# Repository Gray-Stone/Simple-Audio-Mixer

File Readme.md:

# Simple 2-in-1-out Audio Merger
 Design choices and reason for decision  

Overview 
=========

Core feature:
-------------

Simple Audio Merger (SAM) is designed to be used for merging audio from
2 sources and simply output the added voltage to output. Input is design
for common consumer appliances with stereo audio, and there will not be
any processing other than summation on board. The output is only
buffered (powered) by an Opamp, and a power amplifier should be used if
the load is not high impedance (headphone, speaker is typical low
impedance load).

Power Option
============

3.5mm stereo audio jack will be used as audio interface for both input
and output. This is the most common form of audio connection between
desktop device and is simplest.

Power source 
-------------

Possible choice of USB power and battery power.

Benefit of USB supply:

-   Device’s original design is to be used to merge audio from computer
    and gamming console, this means abundant USB supplies.

Problem with USB supply:

-   Huge amount of noise (USB data line, other USB devices, etc.)

-   Single Rail, and the lower rail is mains-earth reference (virtual
    ground cannot be connected with other devices)

Reason to choose battery supply:

-   Clean rail.

-   Easily generated negative rail (or virtual ground).

-   Since floating rail, no requirement before connecting ground with
    other device (virtual or not)

Problem with battery:

-   Need replace battery

-   Need a battery management system to detect low battery and
    shutoff/notice user before it causes problem

The USB high power rail noise is not much of a problem given all signal
goes through Opamp, which have great rail rejection.

The battery replacement is not that bad, this design does not provide
power amplifier. Most power are used by Opamp. So, replacement cycle is
not as often. In addition, audio signal is basically below 1V, two AA
battery will be enough for dual rails.

Both choices are ok, if a battery is chosen, then BMS is needed. If USB
is chosen, negative rail is needed.

Dual Rail generation 
---------------------

If USB power is used, a negative rail must be generated. Generate a half
rail virtual ground is not suitable in this case.

A voltage reference is generally generated by a voltage buffer with
input connect to a revers biased zener. The zener voltage is set by
current, despite little, but still fluctuate with current change. The
source current for zener voltage is usually set by resistor, which is
voltage controlled current.

USB is mains-earth referenced ground. The audio ground from other device
(input and output amplifier) is the same mains-earth reference as well.
This means the virtual ground can not be connected to another device.

When using virtual ground, the output voltage is referenced to virtual
ground. The voltage ripple across “negative rail” and virtual ground is
considered rail noise. However, since other device is also ground
referenced, they see they “negative rail” noise as a noise added to
virtual ground. Since output is referenced to virtual ground, outside
device also see this noise as part of the output signal (instead of
common mode noise).

If battery is used, then a virtual ground is easily generated by
connecting a lead from middle of the two batteries. This virtual ground
will be push pull and very stable in voltage. Furthermore, battery is
floating voltage device, the virtual ground can be connected to any
mains-earth connection. This connection makes it remove some common-mode
noise.

Merge Audio Signal
==================

Resistor Summing Circuit.
-------------------------

Audio signal are generally a voltage signal. One possible choice is to
connect everything through a resistor to a summing point. The resistor
turns the voltage signal into current signal. Then transconductance
amplifier can easily turn that into output voltage.

In this case, the impedance each input device see depends on the
resistance and other device it sees.

Individual Opamp Buffered.
--------------------------

If each input is first buffered by an opamp, then all input device sees
high impedance which is decoupled from others. In the case of a low
impedance (high power) device on input side, buffer Opamp prevent other
input device get loaded.

Decision
========

-   USB power source with negative rail (No BMS required, Opamp have
    good PSRR).

-   Opamp buffered input (Opamp are cheap, this is a one-off board).

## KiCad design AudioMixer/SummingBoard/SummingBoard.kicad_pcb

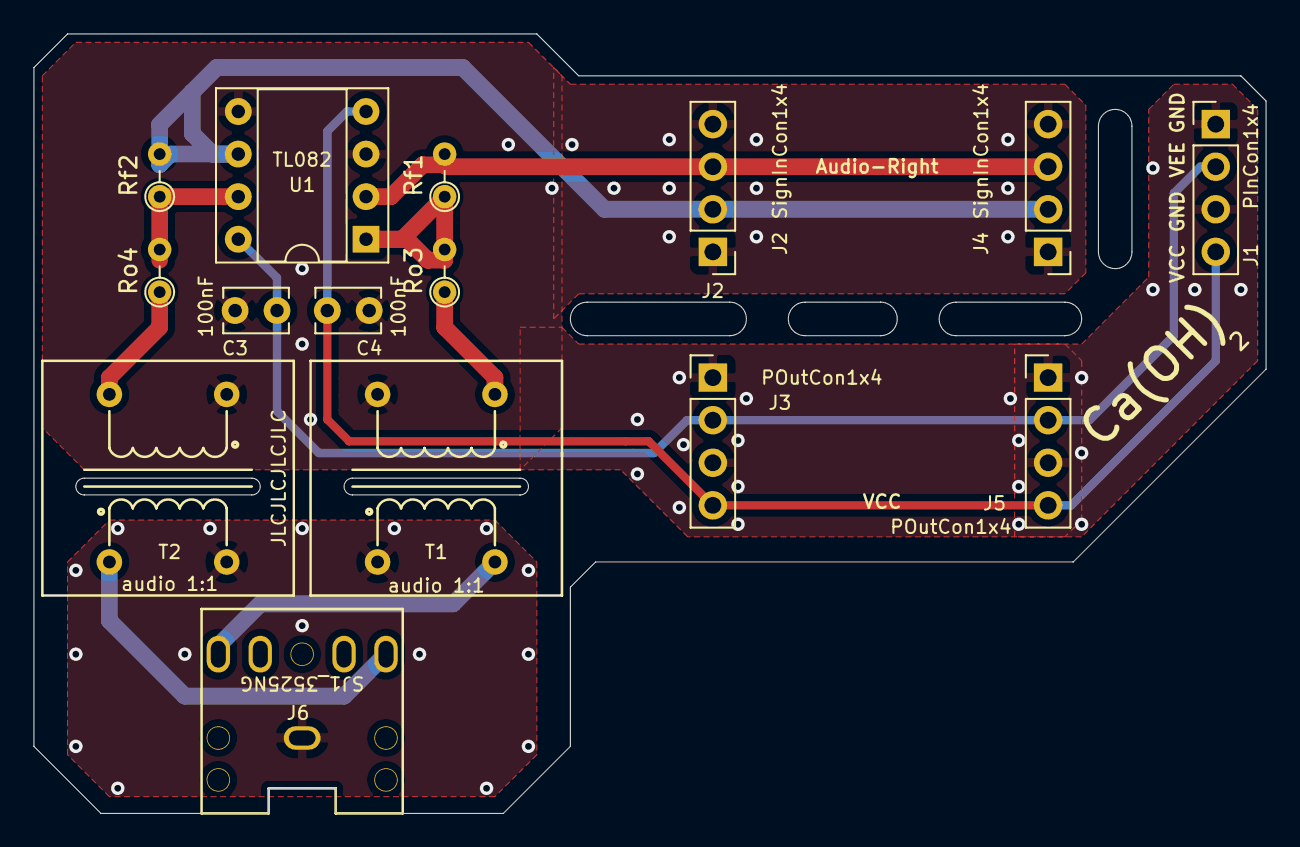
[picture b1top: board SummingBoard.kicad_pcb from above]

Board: 2 copper layers, 73.5 x 46.5 mm, 15 parts (0 on the bottom side), 12 nets.

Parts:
C3, C4: 100nF; C_Disc_D3.8mm_W2.6mm_P2.50mm
J1: PInCon1x4; Socket_Strip_Straight_1x04_Pitch2.54mm
J2, J4: SignInCon1x4; Socket_Strip_Straight_1x04_Pitch2.54mm
J3, J5: POutCon1x4; Socket_Strip_Straight_1x04_Pitch2.54mm
J6: SJ1_3525NG; Audio Barral SJ1-3525NG
Rf1, Rf2: 1k; R_Axial_DIN0204_L3.6mm_D1.6mm_P2.54mm_Vertical
Ro3, Ro4: 100; R_Axial_DIN0204_L3.6mm_D1.6mm_P2.54mm_Vertical
T1, T2: audio 1:1; Audio Transformer
U1: TL082; DIP-8_W7.62mm_Socket

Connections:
/Audio-Left: J2.2, J4.2, Rf2.2, U1.6
/Audio-Right: J2.3, J4.3, Rf1.2, U1.2
/Output_Ground: J6.1, T1.1, T2.2
GND: C3.2, C4.1, J1.1, J1.3, J2.1, J2.4, J3.1, J3.3, J4.1, J4.4, J5.1, J5.3, T1.3, T2.4, U1.3, U1.5
unnamed: J6.2, T2.1
unnamed: J6.3, T1.2
unnamed: Rf1.1, Ro3.2, U1.1
unnamed: Rf2.1, Ro4.2, U1.7
unnamed: Ro3.1, T1.4
unnamed: Ro4.1, T2.3
VCC: C3.1, J1.2, J3.2, J5.2, U1.8
VEE: C4.2, J1.4, J3.4, J5.4, U1.4

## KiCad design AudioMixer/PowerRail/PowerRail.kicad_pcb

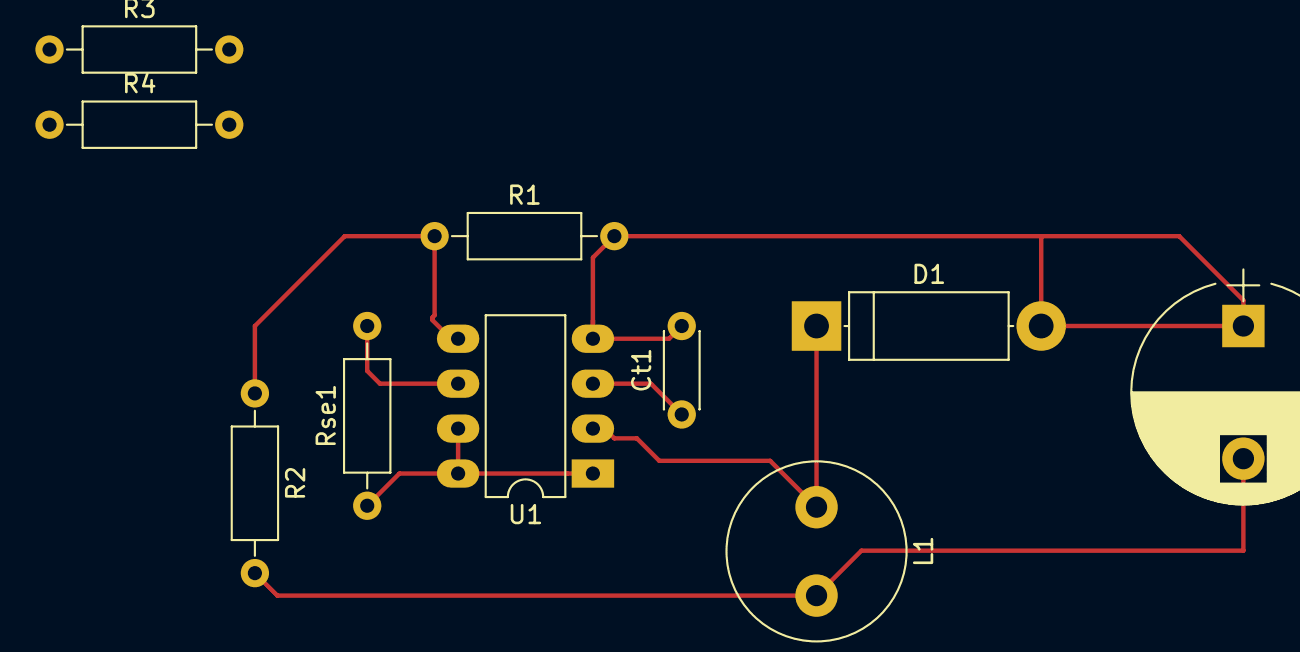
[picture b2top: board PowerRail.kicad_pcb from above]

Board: 2 copper layers, 10 parts (0 on the bottom side), 7 nets.

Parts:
Co1: 2585uF; CP_Radial_D12.5mm_P7.50mm
Ct1: 574pF; C_Disc_D4.3mm_W1.9mm_P5.00mm
D1: 1N4148; D_5W_P12.70mm_Horizontal
L1: 61uH; L_Radial_D10.0mm_P5.00mm_Neosid_SD12_style3
R1: 1k; R_Axial_DIN0207_L6.3mm_D2.5mm_P10.16mm_Horizontal
R2, R3, R4: 3k; R_Axial_DIN0207_L6.3mm_D2.5mm_P10.16mm_Horizontal
Rse1: 0.319; R_Axial_DIN0207_L6.3mm_D2.5mm_P10.16mm_Horizontal
U1: MC34063AP; DIP-8_W7.62mm_LongPads

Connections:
GND: Co1.2, L1.2, R2.2, R3.2
unnamed: Ct1.1, U1.3
unnamed: D1.1, L1.1, U1.2
unnamed: R1.1, R2.1, U1.5
unnamed: Rse1.1, U1.1, U1.7, U1.8
VCC: Rse1.2, U1.6
VEE: Co1.1, Ct1.2, D1.2, R1.2, R4.2, U1.4

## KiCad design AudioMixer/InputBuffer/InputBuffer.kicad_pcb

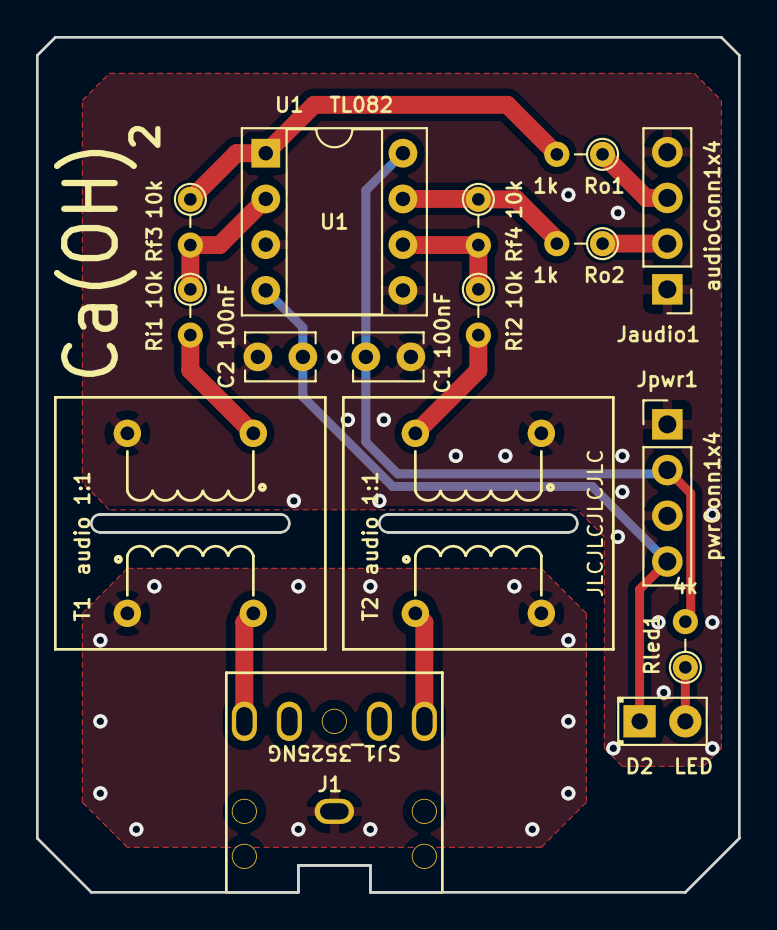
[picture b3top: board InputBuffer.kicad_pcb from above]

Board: 2 copper layers, 39.0 x 47.5 mm, 16 parts (0 on the bottom side), 15 nets.

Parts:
C1, C2: 100nF; C_Disc_D3.8mm_W2.6mm_P2.50mm
D2: LED; LED_D2.0mm_W4.8mm_H2.5mm_FlatTop
J1: SJ1_3525NG; Audio Barral SJ1-3525NG
Jaudio1: audioConn1x4; Socket_Strip_Straight_1x04_Pitch2.54mm
Jpwr1: pwrConn1x4; Socket_Strip_Straight_1x04_Pitch2.54mm
Rf3, Rf4: 10k; R_Axial_DIN0204_L3.6mm_D1.6mm_P2.54mm_Vertical
Ri1, Ri2: 10k; R_Axial_DIN0204_L3.6mm_D1.6mm_P2.54mm_Vertical
Rled1: 4k; R_Axial_DIN0204_L3.6mm_D1.6mm_P2.54mm_Vertical
Ro1, Ro2: 1k; R_Axial_DIN0204_L3.6mm_D1.6mm_P2.54mm_Vertical
T1, T2: audio 1:1; Audio Transformer
U1: TL082; DIP-8_W7.62mm_Socket

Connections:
/Audio-Left: Jaudio1.2, Ro2.1
/Audio-Right: Jaudio1.3, Ro1.1
/Input_Ground: J1.1, T1.1, T2.2
GND: C1.2, C2.1, Jaudio1.1, Jaudio1.4, Jpwr1.1, Jpwr1.3, T1.3, T2.4, U1.3, U1.5
unnamed: D2.2, Rled1.1
unnamed: J1.2, T2.1
unnamed: J1.3, T1.2
unnamed: Rf3.1, Ro1.2, U1.1
unnamed: Rf3.2, Ri1.1, U1.2
unnamed: Rf4.1, Ro2.2, U1.7
unnamed: Rf4.2, Ri2.1, U1.6
unnamed: Ri1.2, T1.4
unnamed: Ri2.2, T2.3
VCC: C1.1, Jpwr1.2, Rled1.2, U1.8
VEE: C2.2, D2.1, Jpwr1.4, U1.4

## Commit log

2020-11-21 Setup project and decision log
2020-11-21 Change markdown filename
2020-11-21 Rename index.md to Readme.md
2020-11-21 Testing markdown image and equation
2020-11-21 using pandoc to convert everything to md before push
2020-11-21 modified pandoc bat file to allow mutiple files
2023-06-11 Move folder around
